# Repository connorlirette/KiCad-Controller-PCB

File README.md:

# KiCad-MIDI-Controller-PCB
Project #68 PCB Controller Design in KiCad

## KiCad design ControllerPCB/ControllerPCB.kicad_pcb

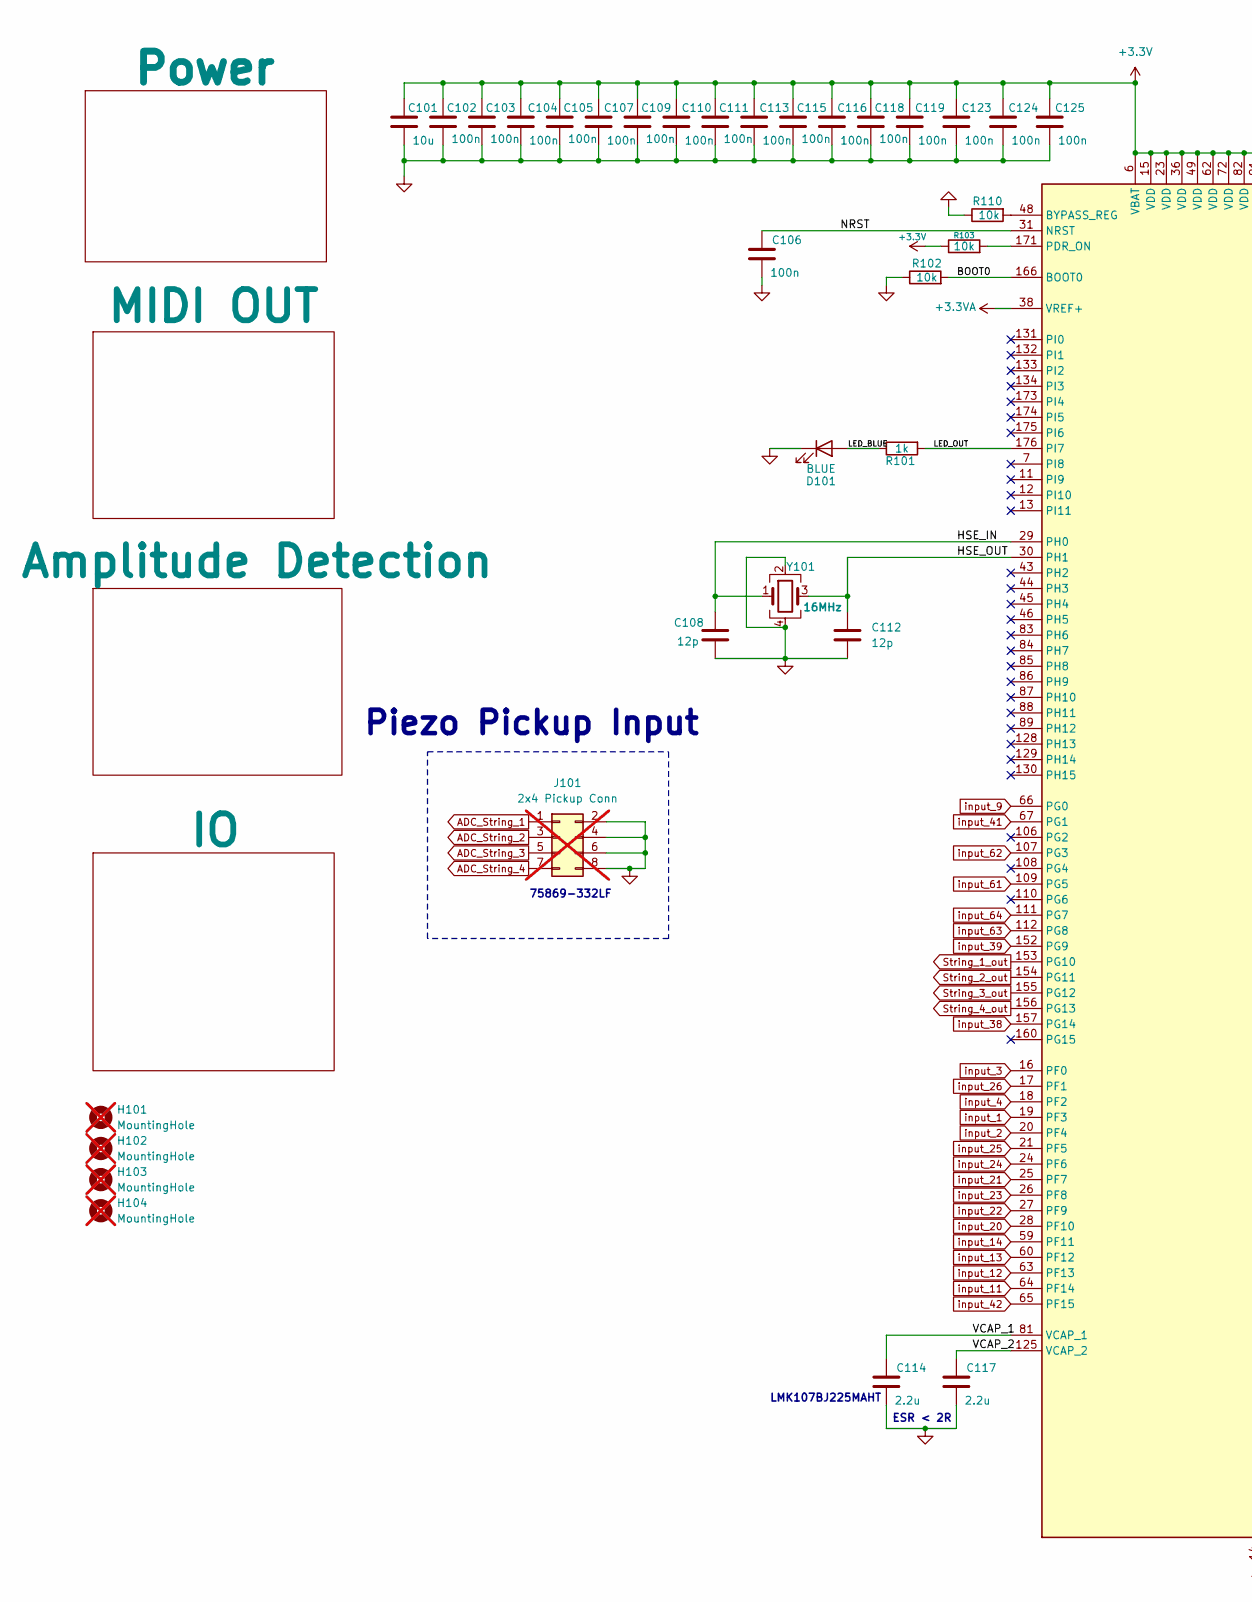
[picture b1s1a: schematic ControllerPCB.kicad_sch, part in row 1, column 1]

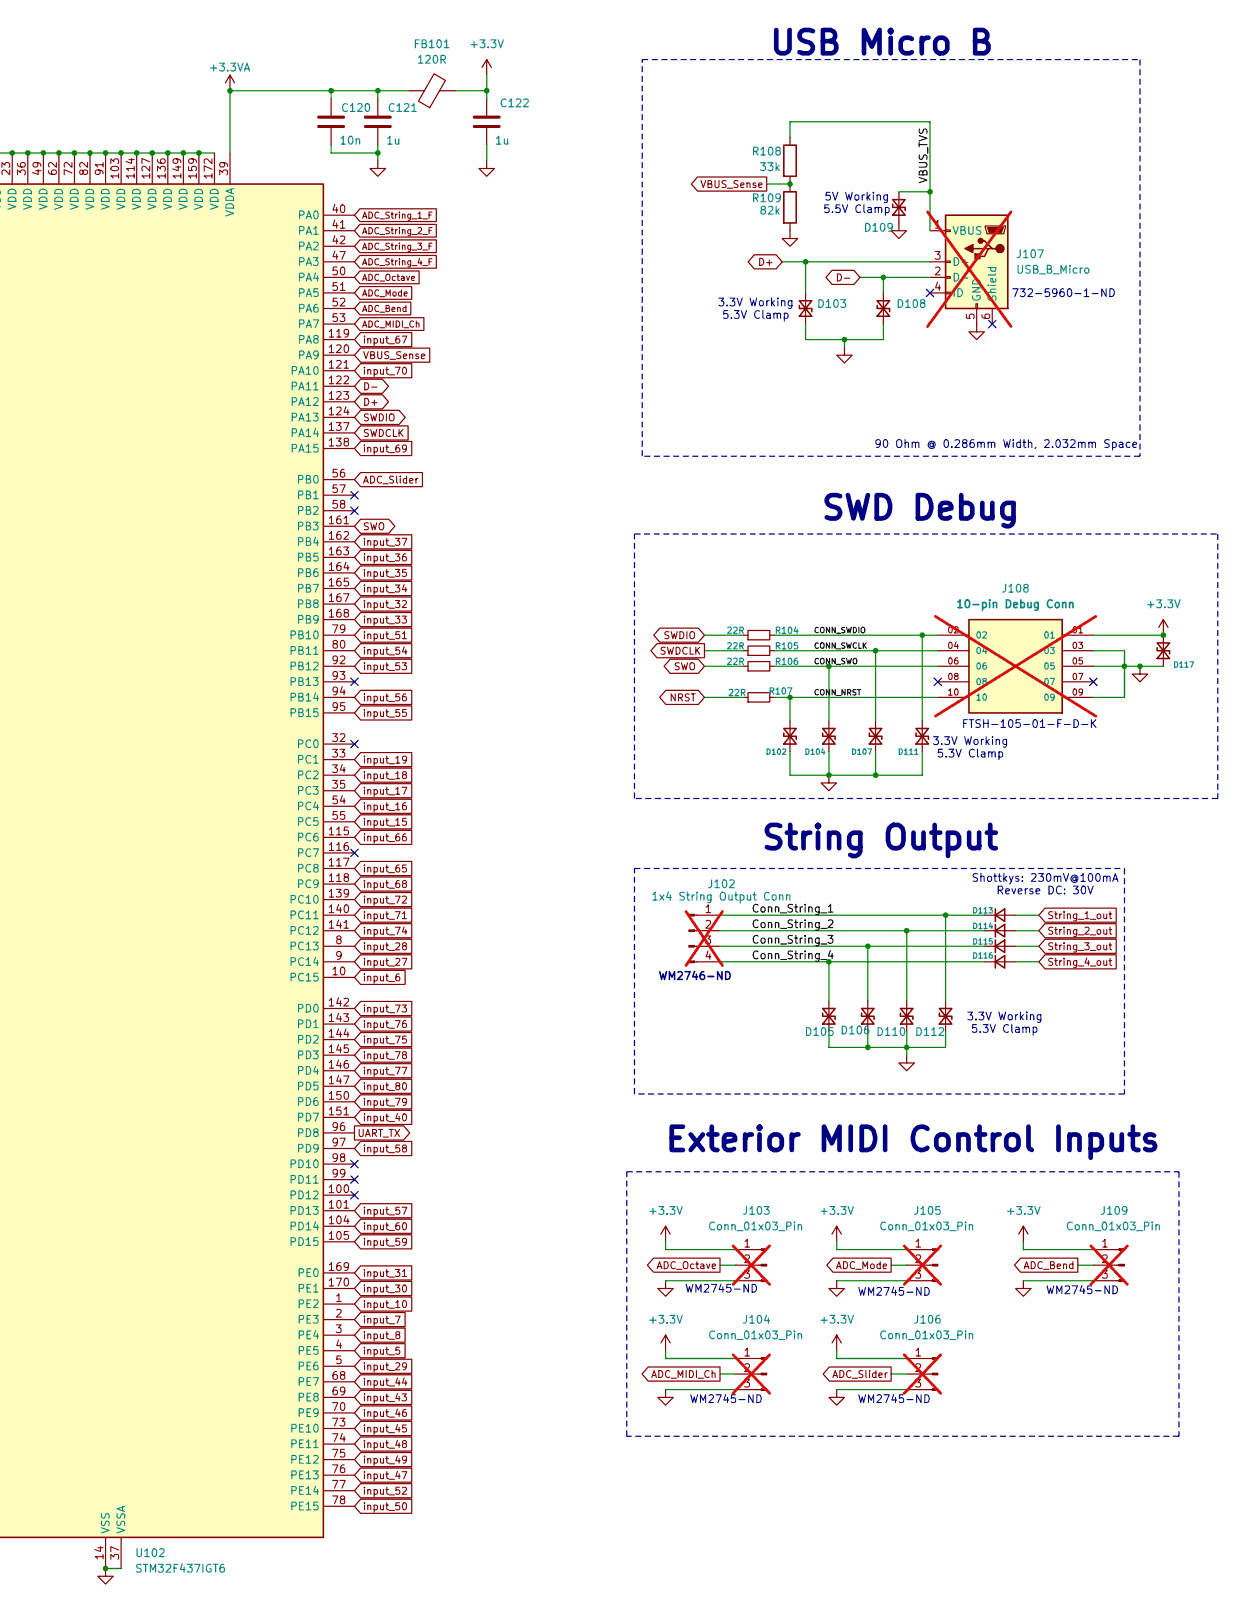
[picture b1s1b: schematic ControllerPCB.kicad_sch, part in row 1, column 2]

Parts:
C101: 10u; C_0603_1608Metric; JLCPCB Part # C19702
C102, C103, C104, C105, C106, C107, C109, C110, C111, C113, C115, C116, C118, C119, C123, C124, C125: 100n; C_0402_1005Metric; JLCPCB Part # C1525
C108, C112: 12p; C_0402_1005Metric; JLCPCB Part # C161304
C114, C117: 2.2u; C_0603_1608Metric; JLCPCB Part # C99228
C120: 10n; C_0402_1005Metric; JLCPCB Part # C60133
C121, C122: 1u; C_0402_1005Metric; JLCPCB Part # C52923
D101: BLUE; LED_0603_1608Metric; JLCPCB Part # C2288
D102, D103, D104, D105, D106, D107, D108, D110, D111, D112, D117: D_TVS_Small; PMEG3005AESFYL; JLCPCB Part # C2908830
D109: D_TVS_VBUS; PMEG3005AESFYL; JLCPCB Part # C2443412
D113, D114, D115, D116: D_Small; D_SOD-323; JLCPCB Part # C146335
FB101: 120R; L_0603_1608Metric; JLCPCB Part # C113030
H101, H102, H103, H104: MountingHole; MountingHole_3.2mm_M3; not fitted
J101: 2x4 Pickup Conn; AMPHENOL_75869-332LF; not fitted
J102: 1x4 String Output Conn; CONN_AE-6410-04A_MOL; not fitted
J103, J104, J105, J106, J109: Conn_01x03_Pin; CONN_AE-6410-03A_MOL; not fitted
J107: USB_B_Micro; USB_Micro-B_Wuerth_629105150521; not fitted
J108: 10-pin Debug Conn; SAMTEC_FTSH-105-01-F-D-K; PARTREV B; not fitted
R101: 1k; R_0402_1005Metric; JLCPCB Part # C11702
R102, R103, R110: 10k; R_0402_1005Metric; JLCPCB Part # C17902
R104, R105, R106, R107: 22R; R_0402_1005Metric; JLCPCB Part # C25092
R108: 33k; R_0402_1005Metric; JLCPCB Part # C25779
R109: 82k; R_0402_1005Metric; JLCPCB Part # C4142
U102: STM32F437IGT6; LQFP-176_24x24mm_P0.5mm
Y101: 16MHz; Crystal_SMD_3225-4Pin_3.2x2.5mm; JLCPCB Part # C13738

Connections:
+3.3V: C101.1, C102.1, C103.1, C104.1, C105.1, C107.1, C109.1, C110.1, C111.1, C113.1, C115.1, C116.1, C118.1, C119.1, C122.1, C123.1, C124.1, C125.1, D117.2 (A2), FB101.2, J103.1, J104.1, J105.1, J106.1, J108.01, J109.1, R103.1, U102.6 (VBAT), U102.15 (VDD), U102.23 (VDD), U102.36 (VDD), U102.49 (VDD), U102.62 (VDD), U102.72 (VDD), U102.82 (VDD), U102.91 (VDD), U102.103 (VDD), U102.114 (VDD), U102.127 (VDD), U102.136 (VDD), U102.149 (VDD), U102.159 (VDD), U102.172 (VDD); also elsewhere on the board
+3.3VA: C120.1, C121.1, FB101.1, U102.38 (VREF+), U102.39 (VDDA)
/BOOT0: R102.2, U102.166 (BOOT0)
/CONN_NRST: D102.2 (A2), J108.10, R107.2
/CONN_SWCLK: D107.2 (A2), J108.04, R105.2
/CONN_SWDIO: D111.2 (A2), J108.02, R104.2
/CONN_SWO: D104.2 (A2), J108.06, R106.2
/Conn_String_1: D112.2 (A2), D113.1 (K), J102.1
/Conn_String_2: D110.2 (A2), D114.1 (K), J102.2
/Conn_String_3: D106.2 (A2), D115.1 (K), J102.3
/Conn_String_4: D105.2 (A2), D116.1 (K), J102.4
/HSE_IN: C108.1, U102.29 (PH0), Y101.1
/HSE_OUT: C112.1, U102.30 (PH1), Y101.3
/LED_BLUE: D101.2 (A), R101.1
/LED_OUT: R101.2, U102.176 (PI7)
/VBUS_TVS: D109.2 (A2), J107.1 (VBUS), R108.1
/VCAP_1: C114.1, U102.81 (VCAP_1)
/VCAP_2: C117.1, U102.125 (VCAP_2)
ADC_Bend: J109.2, U102.52 (PA6)
ADC_MIDI_Ch: J104.2, U102.53 (PA7)
ADC_Mode: J105.2, U102.51 (PA5)
ADC_Octave: J103.2, U102.50 (PA4)
ADC_Slider: J106.2, U102.56 (PB0)
ADC_String_1: J101.1; also elsewhere on the board
ADC_String_1_F: U102.40 (PA0); also elsewhere on the board
ADC_String_2: J101.3; also elsewhere on the board
ADC_String_2_F: U102.41 (PA1); also elsewhere on the board
ADC_String_3: J101.5; also elsewhere on the board
ADC_String_3_F: U102.42 (PA2); also elsewhere on the board
ADC_String_4: J101.7; also elsewhere on the board
ADC_String_4_F: U102.47 (PA3); also elsewhere on the board
D+: D103.2 (A2), J107.3 (D+), U102.123 (PA12)
D-: D108.2 (A2), J107.2 (D-), U102.122 (PA11)
NRST: C106.1, R107.1, U102.31 (NRST)
unnamed: R110.2, U102.48 (BYPASS_REG)
unnamed: R103.2, U102.171 (PDR_ON)
SWDCLK: R105.1, U102.137 (PA14)
SWDIO: R104.1, U102.124 (PA13)
SWO: R106.1, U102.161 (PB3)
String_1_out: D113.2 (A), U102.153 (PG10)
String_2_out: D114.2 (A), U102.154 (PG11)
String_3_out: D115.2 (A), U102.155 (PG12)
String_4_out: D116.2 (A), U102.156 (PG13)
UART_TX: U102.96 (PD8); also elsewhere on the board
VBUS_Sense: R108.2, R109.1, U102.120 (PA9)
input_1: U102.19 (PF3); also elsewhere on the board
input_2: U102.20 (PF4); also elsewhere on the board
input_3: U102.16 (PF0); also elsewhere on the board
input_4: U102.18 (PF2); also elsewhere on the board
input_5: U102.4 (PE5); also elsewhere on the board
input_6: U102.10 (PC15); also elsewhere on the board
input_7: U102.2 (PE3); also elsewhere on the board
input_8: U102.3 (PE4); also elsewhere on the board
input_9: U102.66 (PG0); also elsewhere on the board
input_10: U102.1 (PE2); also elsewhere on the board
input_11: U102.64 (PF14); also elsewhere on the board
input_12: U102.63 (PF13); also elsewhere on the board
input_13: U102.60 (PF12); also elsewhere on the board
input_14: U102.59 (PF11); also elsewhere on the board
input_15: U102.55 (PC5); also elsewhere on the board
input_16: U102.54 (PC4); also elsewhere on the board
input_17: U102.35 (PC3); also elsewhere on the board
input_18: U102.34 (PC2); also elsewhere on the board
input_19: U102.33 (PC1); also elsewhere on the board
input_20: U102.28 (PF10); also elsewhere on the board
input_21: U102.25 (PF7); also elsewhere on the board
input_22: U102.27 (PF9); also elsewhere on the board
input_23: U102.26 (PF8); also elsewhere on the board
input_24: U102.24 (PF6); also elsewhere on the board
input_25: U102.21 (PF5); also elsewhere on the board
input_26: U102.17 (PF1); also elsewhere on the board
input_27: U102.9 (PC14); also elsewhere on the board
input_28: U102.8 (PC13); also elsewhere on the board
input_29: U102.5 (PE6); also elsewhere on the board
input_30: U102.170 (PE1); also elsewhere on the board
input_31: U102.169 (PE0); also elsewhere on the board
input_32: U102.167 (PB8); also elsewhere on the board
input_33: U102.168 (PB9); also elsewhere on the board
input_34: U102.165 (PB7); also elsewhere on the board
input_35: U102.164 (PB6); also elsewhere on the board
input_36: U102.163 (PB5); also elsewhere on the board
input_37: U102.162 (PB4); also elsewhere on the board
input_38: U102.157 (PG14); also elsewhere on the board
input_39: U102.152 (PG9); also elsewhere on the board
input_40: U102.151 (PD7); also elsewhere on the board
input_41: U102.67 (PG1); also elsewhere on the board
input_42: U102.65 (PF15); also elsewhere on the board
input_43: U102.69 (PE8); also elsewhere on the board
input_44: U102.68 (PE7); also elsewhere on the board
input_45: U102.73 (PE10); also elsewhere on the board
input_46: U102.70 (PE9); also elsewhere on the board
input_47: U102.76 (PE13); also elsewhere on the board
input_48: U102.74 (PE11); also elsewhere on the board
input_49: U102.75 (PE12); also elsewhere on the board
input_50: U102.78 (PE15); also elsewhere on the board
input_51: U102.79 (PB10); also elsewhere on the board
input_52: U102.77 (PE14); also elsewhere on the board
input_53: U102.92 (PB12); also elsewhere on the board
input_54: U102.80 (PB11); also elsewhere on the board
input_55: U102.95 (PB15); also elsewhere on the board
input_56: U102.94 (PB14); also elsewhere on the board
input_57: U102.101 (PD13); also elsewhere on the board
input_58: U102.97 (PD9); also elsewhere on the board
input_59: U102.105 (PD15); also elsewhere on the board
input_60: U102.104 (PD14); also elsewhere on the board
input_61: U102.109 (PG5); also elsewhere on the board
input_62: U102.107 (PG3); also elsewhere on the board
input_63: U102.112 (PG8); also elsewhere on the board
input_64: U102.111 (PG7); also elsewhere on the board
input_65: U102.117 (PC8); also elsewhere on the board
input_66: U102.115 (PC6); also elsewhere on the board
input_67: U102.119 (PA8); also elsewhere on the board
input_68: U102.118 (PC9); also elsewhere on the board
input_69: U102.138 (PA15); also elsewhere on the board
input_70: U102.121 (PA10); also elsewhere on the board
input_71: U102.140 (PC11); also elsewhere on the board
input_72: U102.139 (PC10); also elsewhere on the board
input_73: U102.142 (PD0); also elsewhere on the board
input_74: U102.141 (PC12); also elsewhere on the board
input_75: U102.144 (PD2); also elsewhere on the board
input_76: U102.143 (PD1); also elsewhere on the board
input_77: U102.146 (PD4); also elsewhere on the board
input_78: U102.145 (PD3); also elsewhere on the board
input_79: U102.150 (PD6); also elsewhere on the board
input_80: U102.147 (PD5); also elsewhere on the board

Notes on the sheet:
3.3V Working 5.3V Clamp
LMK107BJ225MAHT
90 Ohm @ 0.286mm Width, 2.032mm Space
SWD Debug
75869-332LF
ESR < 2R
WM2745-ND
Shottkys: 230mV@100mA Reverse DC: 30V
WM2746-ND
String Output
Piezo Pickup Input
5V Working 5.5V Clamp
732-5960-1-ND
FTSH-105-01-F-D-K
Exterior MIDI Control Inputs
USB Micro B

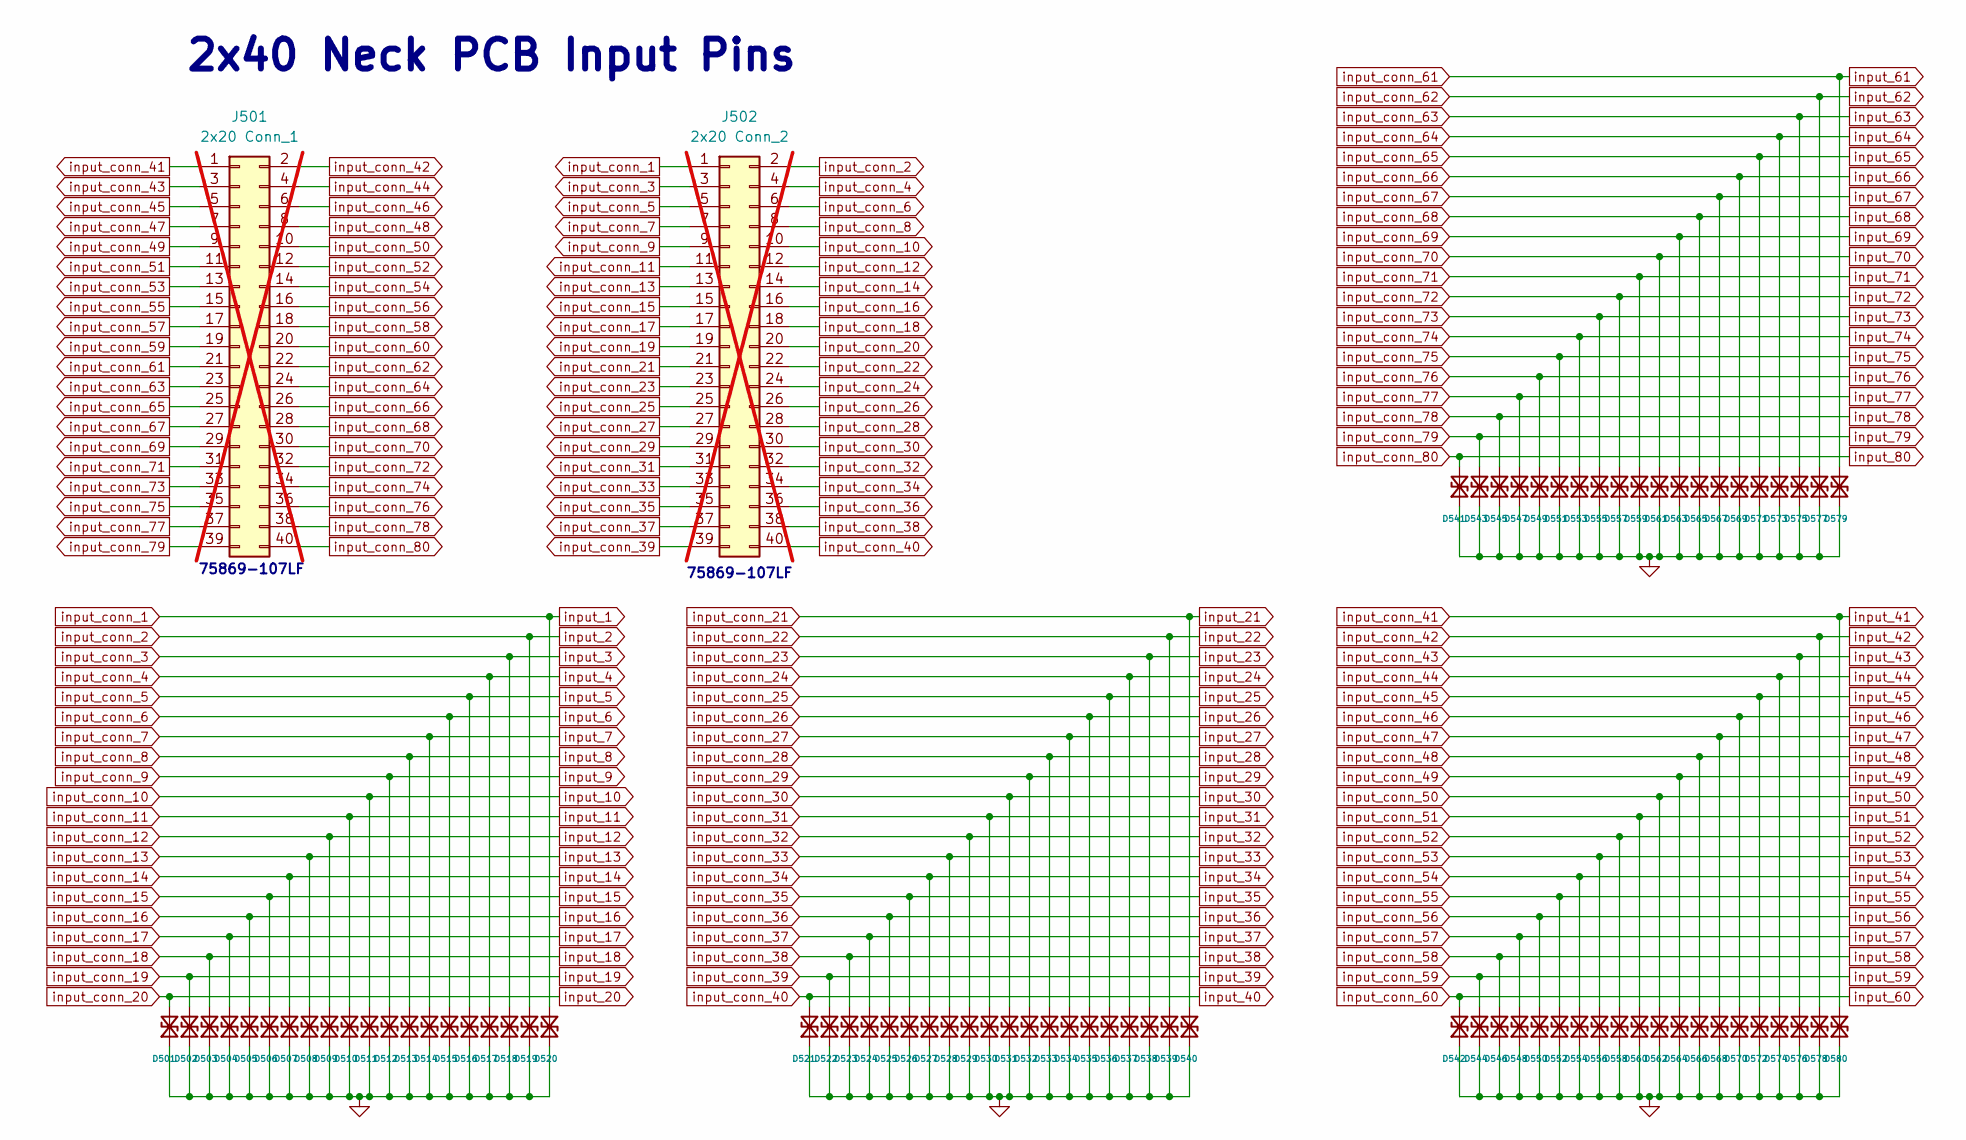
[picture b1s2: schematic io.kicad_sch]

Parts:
D501, D502, D503, D504, D505, D506, D507, D508, D509, D510, D511, D512, D513, D514, D515, D516, D517, D518, D519, D520, D521, D522, D523, D524, D525, D526, D527, D528, D529, D530, D531, D532, D533, D534, D535, D536, D537, D538, D539, D540, D541, D542, D543, D544, D545, D546, D547, D548, D549, D550, D551, D552, D553, D554, D555, D556, D557, D558, D559, D560, D561, D562, D563, D564, D565, D566, D567, D568, D569, D570, D571, D572, D573, D574, D575, D576, D577, D578, D579, D580: D_TVS_Small; PMEG3005AESFYL; JLCPCB Part # C2908830
J501: 2x20 Conn_1; SHDR40W62P254_2X20_5801X920X957P; not fitted
J502: 2x20 Conn_2; SHDR40W62P254_2X20_5801X920X957P; not fitted

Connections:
input_1: D520.2 (A2), J502.1; also elsewhere on the board
input_2: D519.2 (A2), J502.2; also elsewhere on the board
input_3: D518.2 (A2), J502.3; also elsewhere on the board
input_4: D517.2 (A2), J502.4; also elsewhere on the board
input_5: D516.2 (A2), J502.5; also elsewhere on the board
input_6: D515.2 (A2), J502.6; also elsewhere on the board
input_7: D514.2 (A2), J502.7; also elsewhere on the board
input_8: D513.2 (A2), J502.8; also elsewhere on the board
input_9: D512.2 (A2), J502.9; also elsewhere on the board
input_10: D511.2 (A2), J502.10; also elsewhere on the board
input_11: D510.2 (A2), J502.11; also elsewhere on the board
input_12: D509.2 (A2), J502.12; also elsewhere on the board
input_13: D508.2 (A2), J502.13; also elsewhere on the board
input_14: D507.2 (A2), J502.14; also elsewhere on the board
input_15: D506.2 (A2), J502.15; also elsewhere on the board
input_16: D505.2 (A2), J502.16; also elsewhere on the board
input_17: D504.2 (A2), J502.17; also elsewhere on the board
input_18: D503.2 (A2), J502.18; also elsewhere on the board
input_19: D502.2 (A2), J502.19; also elsewhere on the board
input_20: D501.2 (A2), J502.20; also elsewhere on the board
input_21: D540.2 (A2), J502.21; also elsewhere on the board
input_22: D539.2 (A2), J502.22; also elsewhere on the board
input_23: D538.2 (A2), J502.23; also elsewhere on the board
input_24: D537.2 (A2), J502.24; also elsewhere on the board
input_25: D536.2 (A2), J502.25; also elsewhere on the board
input_26: D535.2 (A2), J502.26; also elsewhere on the board
input_27: D534.2 (A2), J502.27; also elsewhere on the board
input_28: D533.2 (A2), J502.28; also elsewhere on the board
input_29: D532.2 (A2), J502.29; also elsewhere on the board
input_30: D531.2 (A2), J502.30; also elsewhere on the board
input_31: D530.2 (A2), J502.31; also elsewhere on the board
input_32: D529.2 (A2), J502.32; also elsewhere on the board
input_33: D528.2 (A2), J502.33; also elsewhere on the board
input_34: D527.2 (A2), J502.34; also elsewhere on the board
input_35: D526.2 (A2), J502.35; also elsewhere on the board
input_36: D525.2 (A2), J502.36; also elsewhere on the board
input_37: D524.2 (A2), J502.37; also elsewhere on the board
input_38: D523.2 (A2), J502.38; also elsewhere on the board
input_39: D522.2 (A2), J502.39; also elsewhere on the board
input_40: D521.2 (A2), J502.40; also elsewhere on the board
input_41: D580.2 (A2), J501.1; also elsewhere on the board
input_42: D578.2 (A2), J501.2; also elsewhere on the board
input_43: D576.2 (A2), J501.3; also elsewhere on the board
input_44: D574.2 (A2), J501.4; also elsewhere on the board
input_45: D572.2 (A2), J501.5; also elsewhere on the board
input_46: D570.2 (A2), J501.6; also elsewhere on the board
input_47: D568.2 (A2), J501.7; also elsewhere on the board
input_48: D566.2 (A2), J501.8; also elsewhere on the board
input_49: D564.2 (A2), J501.9; also elsewhere on the board
input_50: D562.2 (A2), J501.10; also elsewhere on the board
input_51: D560.2 (A2), J501.11; also elsewhere on the board
input_52: D558.2 (A2), J501.12; also elsewhere on the board
input_53: D556.2 (A2), J501.13; also elsewhere on the board
input_54: D554.2 (A2), J501.14; also elsewhere on the board
input_55: D552.2 (A2), J501.15; also elsewhere on the board
input_56: D550.2 (A2), J501.16; also elsewhere on the board
input_57: D548.2 (A2), J501.17; also elsewhere on the board
input_58: D546.2 (A2), J501.18; also elsewhere on the board
input_59: D544.2 (A2), J501.19; also elsewhere on the board
input_60: D542.2 (A2), J501.20; also elsewhere on the board
input_61: D579.2 (A2), J501.21; also elsewhere on the board
input_62: D577.2 (A2), J501.22; also elsewhere on the board
input_63: D575.2 (A2), J501.23; also elsewhere on the board
input_64: D573.2 (A2), J501.24; also elsewhere on the board
input_65: D571.2 (A2), J501.25; also elsewhere on the board
input_66: D569.2 (A2), J501.26; also elsewhere on the board
input_67: D567.2 (A2), J501.27; also elsewhere on the board
input_68: D565.2 (A2), J501.28; also elsewhere on the board
input_69: D563.2 (A2), J501.29; also elsewhere on the board
input_70: D561.2 (A2), J501.30; also elsewhere on the board
input_71: D559.2 (A2), J501.31; also elsewhere on the board
input_72: D557.2 (A2), J501.32; also elsewhere on the board
input_73: D555.2 (A2), J501.33; also elsewhere on the board
input_74: D553.2 (A2), J501.34; also elsewhere on the board
input_75: D551.2 (A2), J501.35; also elsewhere on the board
input_76: D549.2 (A2), J501.36; also elsewhere on the board
input_77: D547.2 (A2), J501.37; also elsewhere on the board
input_78: D545.2 (A2), J501.38; also elsewhere on the board
input_79: D543.2 (A2), J501.39; also elsewhere on the board
input_80: D541.2 (A2), J501.40; also elsewhere on the board

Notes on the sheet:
75869-107LF
2x40 Neck PCB Input Pins

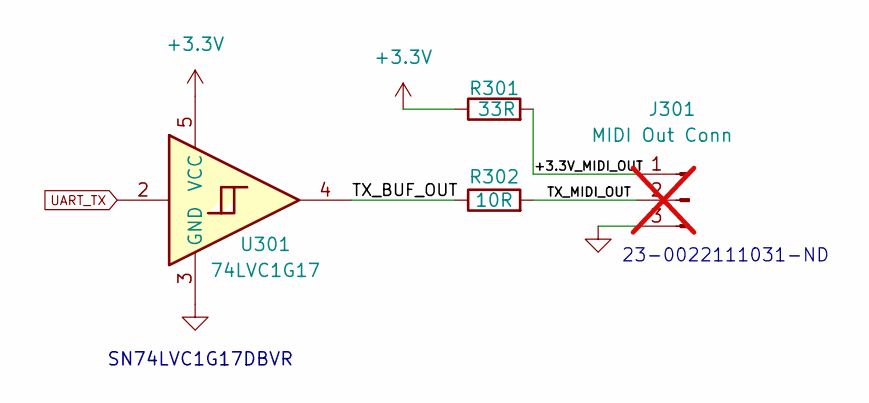
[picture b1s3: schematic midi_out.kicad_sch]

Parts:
J301: MIDI Out Conn; CONN_AE-6410-03A_MOL; not fitted
R301: 33R; R_0402_1005Metric; JLCPCB Part # C25105
R302: 10R; R_0402_1005Metric; JLCPCB Part # C25077
U301: 74LVC1G17; SOT95P280X145-5N; JLCPCB Part # C7836

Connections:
+3.3V: R301.1, U301.5 (VCC); also elsewhere on the board
/MIDI OUT/+3.3V_MIDI_OUT: J301.1, R301.2
/MIDI OUT/TX_BUF_OUT: R302.1, U301.4
/MIDI OUT/TX_MIDI_OUT: J301.2, R302.2
UART_TX: U301.2; also elsewhere on the board

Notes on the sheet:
23-0022111031-ND
SN74LVC1G17DBVR

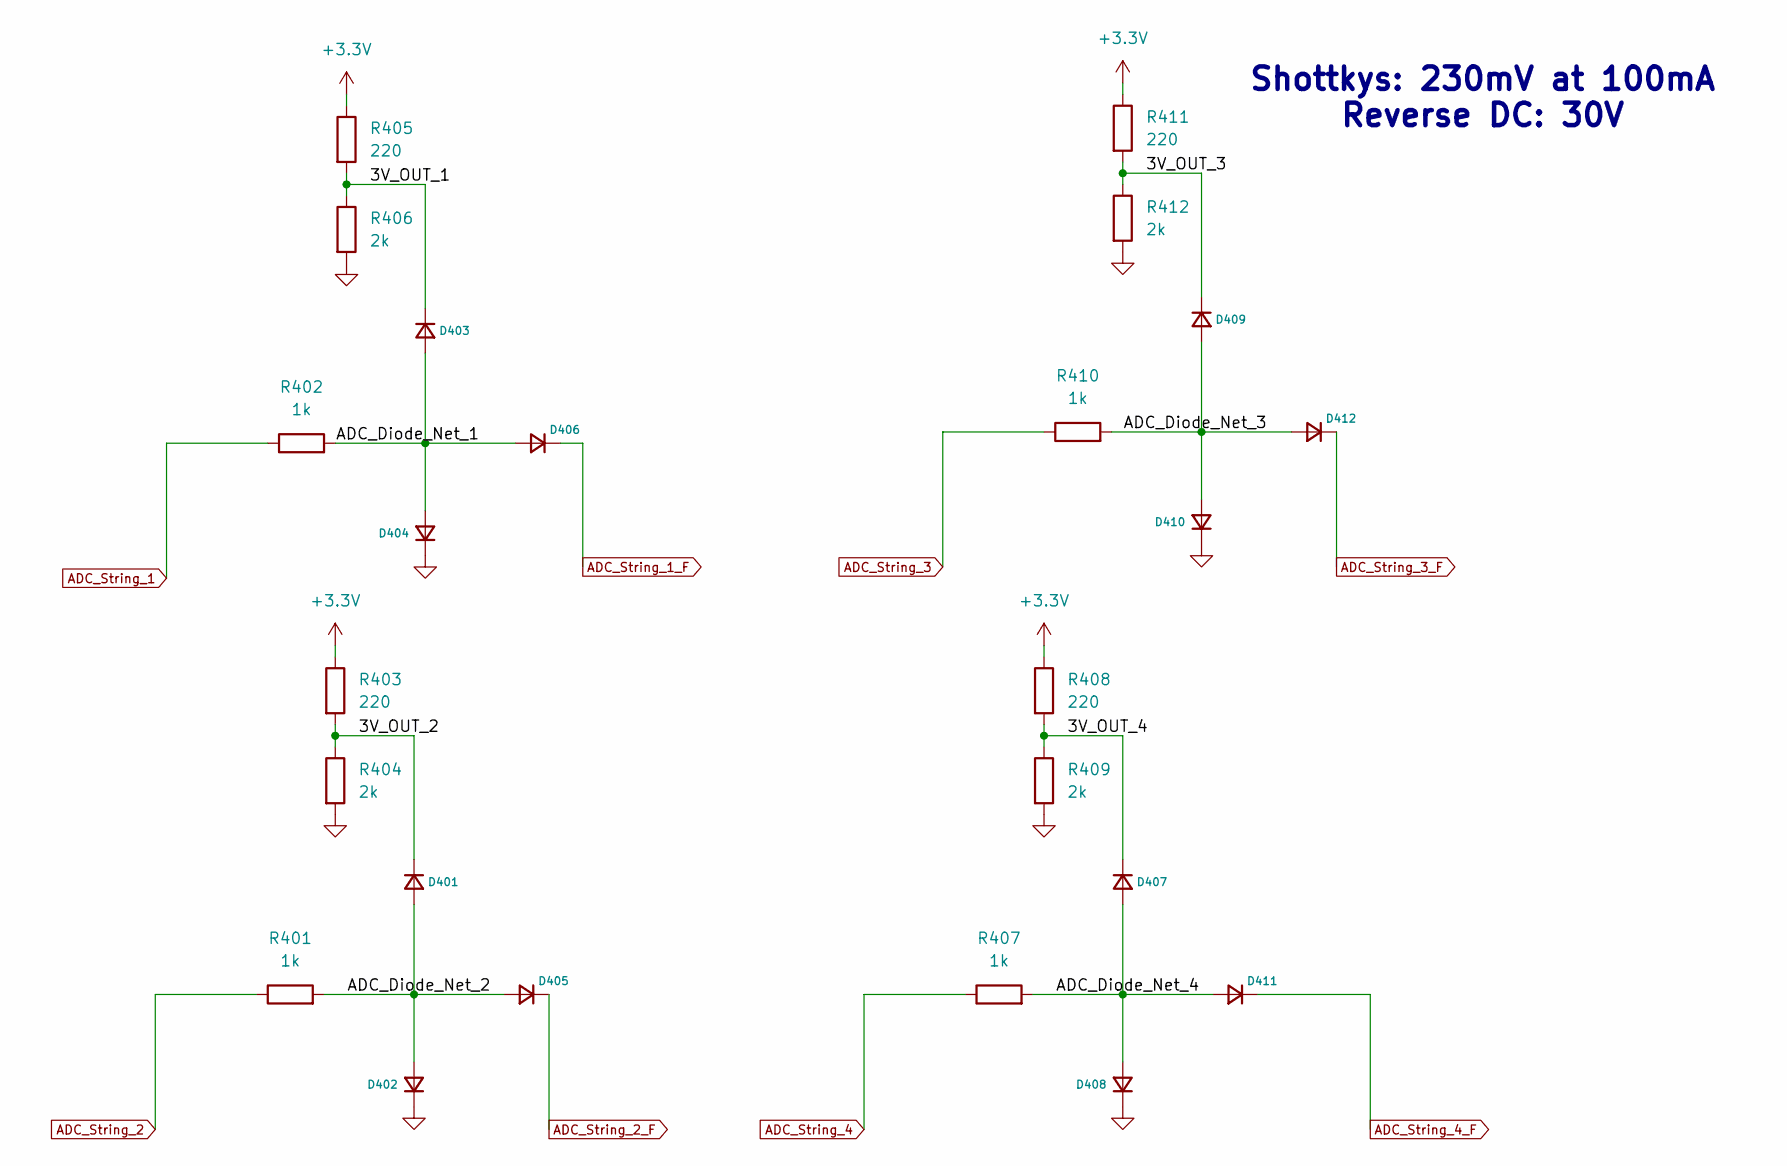
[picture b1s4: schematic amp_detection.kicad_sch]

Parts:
D401, D402, D403, D404, D405, D406, D407, D408, D409, D410, D411, D412: D_Small; D_SOD-323; JLCPCB Part # C146335
R401, R402, R407, R410: 1k; R_0402_1005Metric; JLCPCB Part # C11702
R403, R405, R408, R411: 220; R_0402_1005Metric; JLCPCB Part # C25091
R404, R406, R409, R412: 2k; R_0402_1005Metric; JLCPCB Part # C4109

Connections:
+3.3V: R403.1, R405.1, R408.1, R411.1; also elsewhere on the board
/Amplitude Detection/3V_OUT_1: D403.1 (K), R405.2, R406.1
/Amplitude Detection/3V_OUT_2: D401.1 (K), R403.2, R404.1
/Amplitude Detection/3V_OUT_3: D409.1 (K), R411.2, R412.1
/Amplitude Detection/3V_OUT_4: D407.1 (K), R408.2, R409.1
/Amplitude Detection/ADC_Diode_Net_1: D403.2 (A), D404.2 (A), D406.2 (A), R402.2
/Amplitude Detection/ADC_Diode_Net_2: D401.2 (A), D402.2 (A), D405.2 (A), R401.2
/Amplitude Detection/ADC_Diode_Net_3: D409.2 (A), D410.2 (A), D412.2 (A), R410.2
/Amplitude Detection/ADC_Diode_Net_4: D407.2 (A), D408.2 (A), D411.2 (A), R407.2
ADC_String_1: R402.1; also elsewhere on the board
ADC_String_1_F: D406.1 (K); also elsewhere on the board
ADC_String_2: R401.1; also elsewhere on the board
ADC_String_2_F: D405.1 (K); also elsewhere on the board
ADC_String_3: R410.1; also elsewhere on the board
ADC_String_3_F: D412.1 (K); also elsewhere on the board
ADC_String_4: R407.1; also elsewhere on the board
ADC_String_4_F: D411.1 (K); also elsewhere on the board

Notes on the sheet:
Shottkys: 230mV at 100mA Reverse DC: 30V

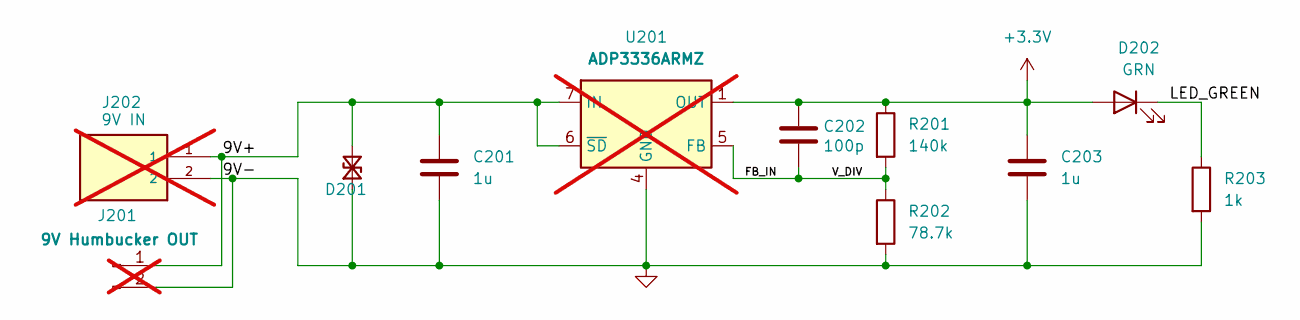
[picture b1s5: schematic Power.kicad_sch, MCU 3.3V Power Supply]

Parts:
C201, C203: 1u; C_0402_1005Metric; JLCPCB Part # C52923
C202: 100p; C_0402_1005Metric; JLCPCB Part # C1546
D201: D_TVS_Small; PMEG3005AESFYL; JLCPCB Part # C2908830
D202: GRN; LED_0603_1608Metric; JLCPCB Part # C22371297
J201: 9V Humbucker OUT; TE_3-641126-2; not fitted
J202: 9V IN; APP_ASMPR45-1X2-RK; PARTREV N/A; not fitted
R201: 140k; R_0402_1005Metric; JLCPCB Part # C2998127
R202: 78.7k; R_0402_1005Metric; JLCPCB Part # C852915
R203: 1k; R_0402_1005Metric; JLCPCB Part # C11702
U201: ADP3336ARMZ; RM_8_ADI; not fitted

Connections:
+3.3V: C202.1, C203.1, D202.2 (A), R201.1, U201.1 (OUT), U201.2 (OUT), U201.3 (OUT); also elsewhere on the board
/Power/FB_IN: C202.2, R201.2, R202.1, U201.5 (FB)
/Power/LED_GREEN: D202.1 (K), R203.1

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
